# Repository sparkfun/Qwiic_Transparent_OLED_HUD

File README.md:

SparkFun Qwiic Transparent OLED HUD
========================================

[*SparkFun Qwiic Transparent OLED HUD Hookup Guide (LCD-15079)*](https://www.sparkfun.com/products/14691)

Qwiic Breakout for the WiseChip US-0011GMIAG01 OLED HUD. Clear screens are no longer a thing of the Sci-Fi world! The Qwiic Transparent OLED HUD is SparkFun's answer to all of your futuristic transparent HUD needs. Designed for use in vehicle heads-up displays, this OLED panel is brilliant in the dark but easily visible in daylight. The display is "area colored" meaning that while no one segment can change colors, there are different colored segments on the display.

Repository Contents
-------------------

* **/Hardware** - Eagle design files (.brd, .sch)
* **/Production** - Production panel files (.brd)

Documentation
--------------
* **[Library](https://github.com/sparkfun/SparkFun_WiseChip_HUD_Library)** - Arduino library
* **[Hookup Guide](https://learn.sparkfun.com/tutorials/qwiic-transparent-oled-hud-hookup-guide)** - Basic hookup guide

Product Versions
----------------

* **[LCD-15079](https://www.sparkfun.com/products/15079)** - SparkFun Red Version
* **[SPX-14691](https://www.sparkfun.com/products/14691)** - SparkX Version

License Information
-------------------

This product is _**open source**_! 

Please review the LICENSE.md file for license information. 

If you have any questions or concerns on licensing, please contact techsupport@sparkfun.com.

Distributed as-is; no warranty is given.

- Your friends at SparkFun.

_<COLLABORATION CREDIT>_

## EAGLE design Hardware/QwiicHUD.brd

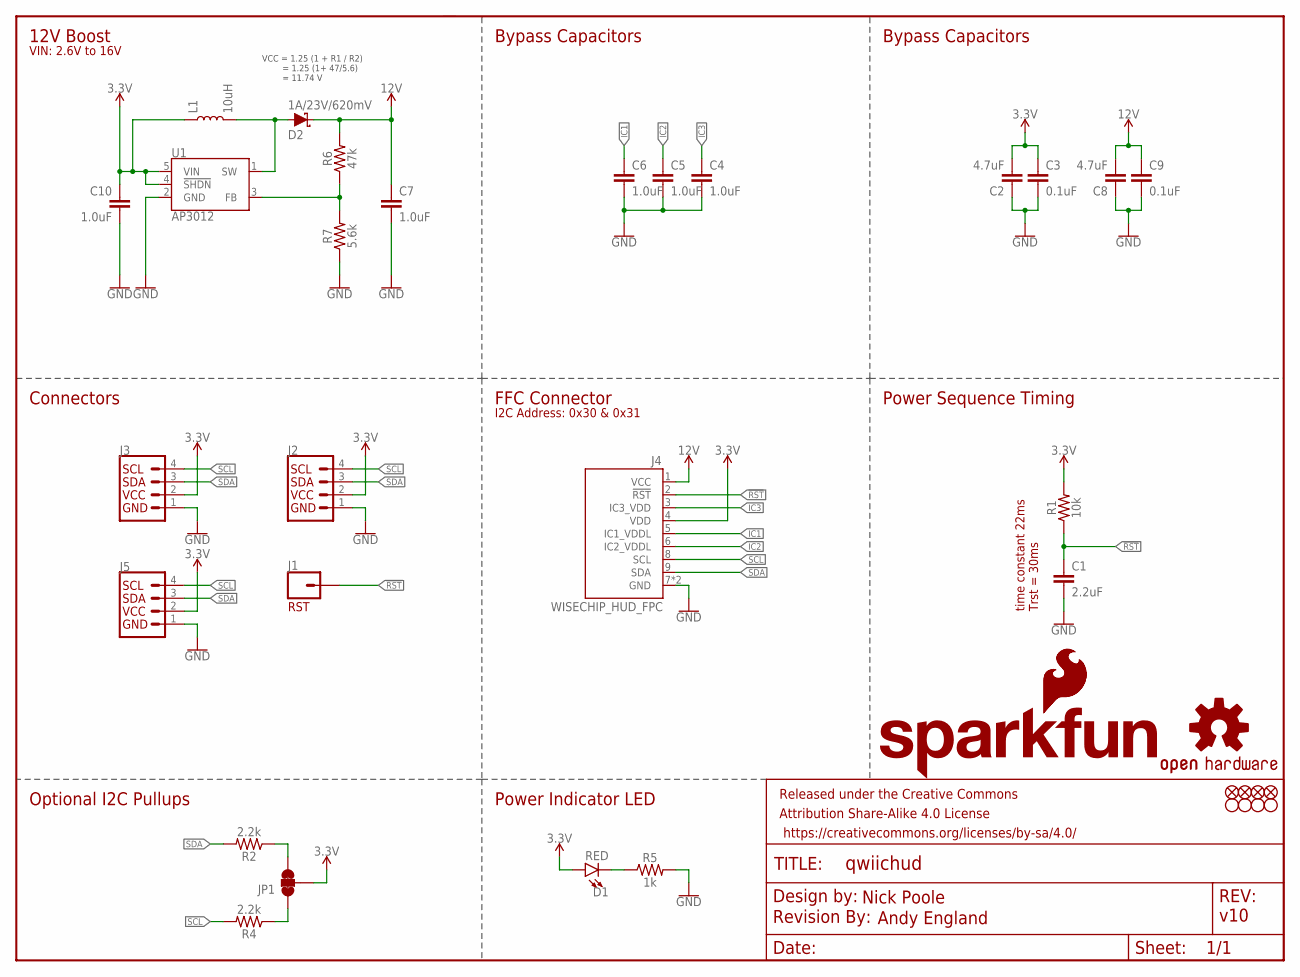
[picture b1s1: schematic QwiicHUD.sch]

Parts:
C1: 2.2uF; 0603
C2, C8: 4.7uF; 0603
C3, C9: 0.1uF; 0603
C4, C5, C6, C10: 1.0uF; 0603
C7: 1.0uF; 0805
D1: RED; LED-0603
D2: 1A/23V/620mV; SOD-323
FD1, FD2, FD3, FD4: FIDUCIALUFIDUCIAL; FIDUCIAL-MICRO
FRAME1: FRAME-LETTER; CREATIVE_COMMONS
H1, H2, H3, H4: STAND-OFF
J1: CONN_01PTH_NO_SILK_YES_STOP; 1X01_NO_SILK
J2: I2C_STANDARD_NO_SILK; 1X04_NO_SILK
J3, J5: QWIIC_CONNECTORJS-1MM; 1X04_1MM_RA
J4: WISECHIP_HUD_FPC; SERIES6288
JP1: JUMPER-SMT_3_2-NC_TRACE_SILK; SMT-JUMPER_3_2-NC_TRACE_SILK
L1: 10uH; INDUCTOR_4.7UH
LOGO1: OSHW-LOGOS; OSHW-LOGO-S
LOGO2: SFE_LOGO_NAME_FLAME.1_INCH; SFE_LOGO_NAME_FLAME_.1
LOGO3: SFE_LOGO_FLAME.1_INCH; SFE_LOGO_FLAME_.1
LOGO4: REVISION
R1: 10k; 0603
R2, R4: 2.2k; 0603
R5: 1k; 0603
R6: 47k; 0603
R7: 5.6k; 0603
U1: AP3012; SOT23-5

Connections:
3.3V: C2.2, C3.1, C10.1, D1.A, J2.2 (VCC), J3.2, J4.4 (VDD), J5.2, JP1.2, L1.P$1 (1), R1.2, U1.4 (!SHDN!), U1.5 (VIN)
12V: C7.1, C8.2, C9.1, D2.C, J4.1 (VCC), R6.2
!RST: C1.1, J1.1, J4.2 (!RST), R1.1
GND: C1.2, C2.1, C3.2, C4.2, C5.2, C6.2, C7.2, C8.1, C9.2, C10.2, J2.1 (GND), J3.1, J4.7 (GND), J4.10 (GND), J5.1, R5.2, R7.1, U1.2 (GND)
IC1: C6.1, J4.5 (IC1_VDDL)
IC2: C5.1, J4.6 (IC2_VDDL)
IC3: C4.1, J4.3 (IC3_VDD)
unnamed: JP1.3, R2.1
unnamed: JP1.1, R4.1
unnamed: D1.C, R5.1
unnamed: D2.A, L1.P$2 (2), U1.1 (SW)
unnamed: R6.1, R7.2, U1.3 (FB)
SCL: J2.4 (SCL), J3.4, J4.8 (SCL), J5.4, R4.2
SDA: J2.3 (SDA), J3.3, J4.9 (SDA), J5.3, R2.2

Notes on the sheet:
time constant 22ms Trst = 30ms
FFC Connector
Connectors
Power Sequence Timing
Optional I2C Pullups
RST
Power Indicator LED
VCC = 1.25 (1 + R1 / R2) = 1.25 (1+ 47/5.6) = 11.74 V
12V Boost
Nick Poole
Andy England
v10
VIN: 2.6V to 16V
I2C Address: 0x30 & 0x31
Bypass Capacitors

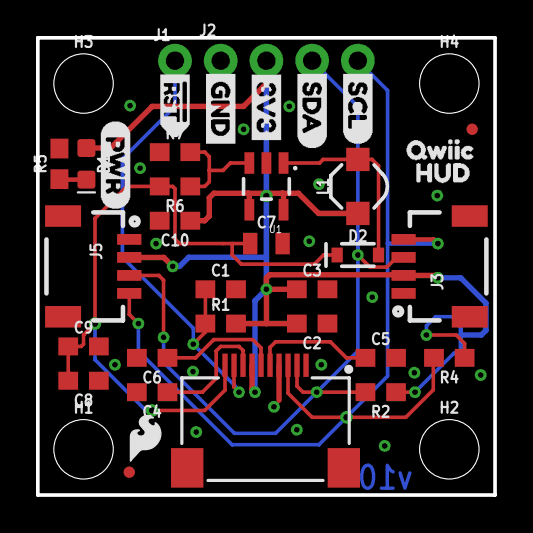
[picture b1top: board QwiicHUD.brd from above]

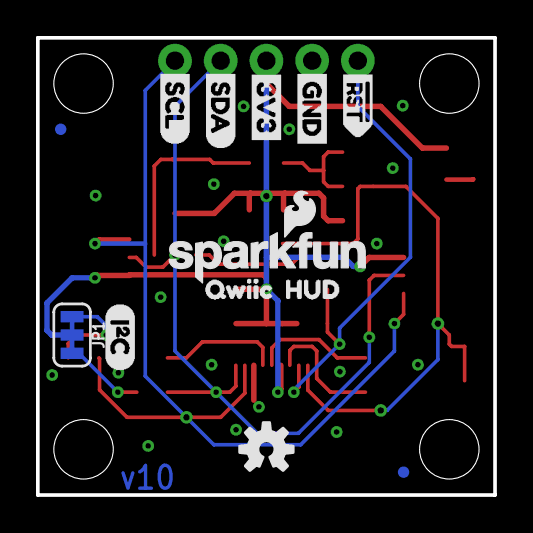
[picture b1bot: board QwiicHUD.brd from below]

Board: 2 copper layers, 25.4 x 25.4 mm, 55 parts (13 on the bottom side), 14 nets.

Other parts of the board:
U$1, U$14: #RST>
U$2, U$18: QWIIC0
U$3, U$19: HUD1
U$5, U$13: GND
U$6, U$12: 3V3
U$7, U$10: SDA
U$8, U$11: SCL
U$9: (PWR)
U$20: (I_SUPER2_C)

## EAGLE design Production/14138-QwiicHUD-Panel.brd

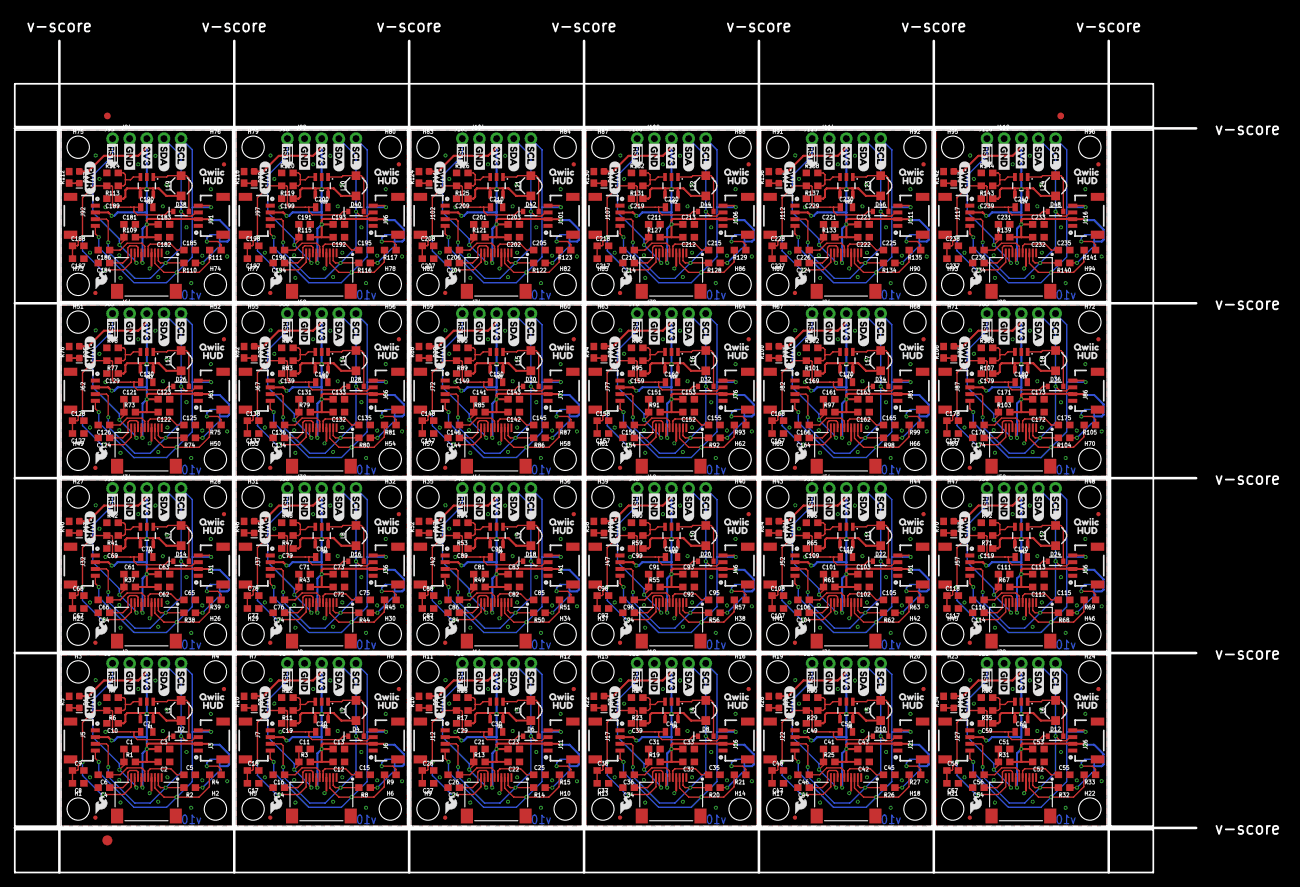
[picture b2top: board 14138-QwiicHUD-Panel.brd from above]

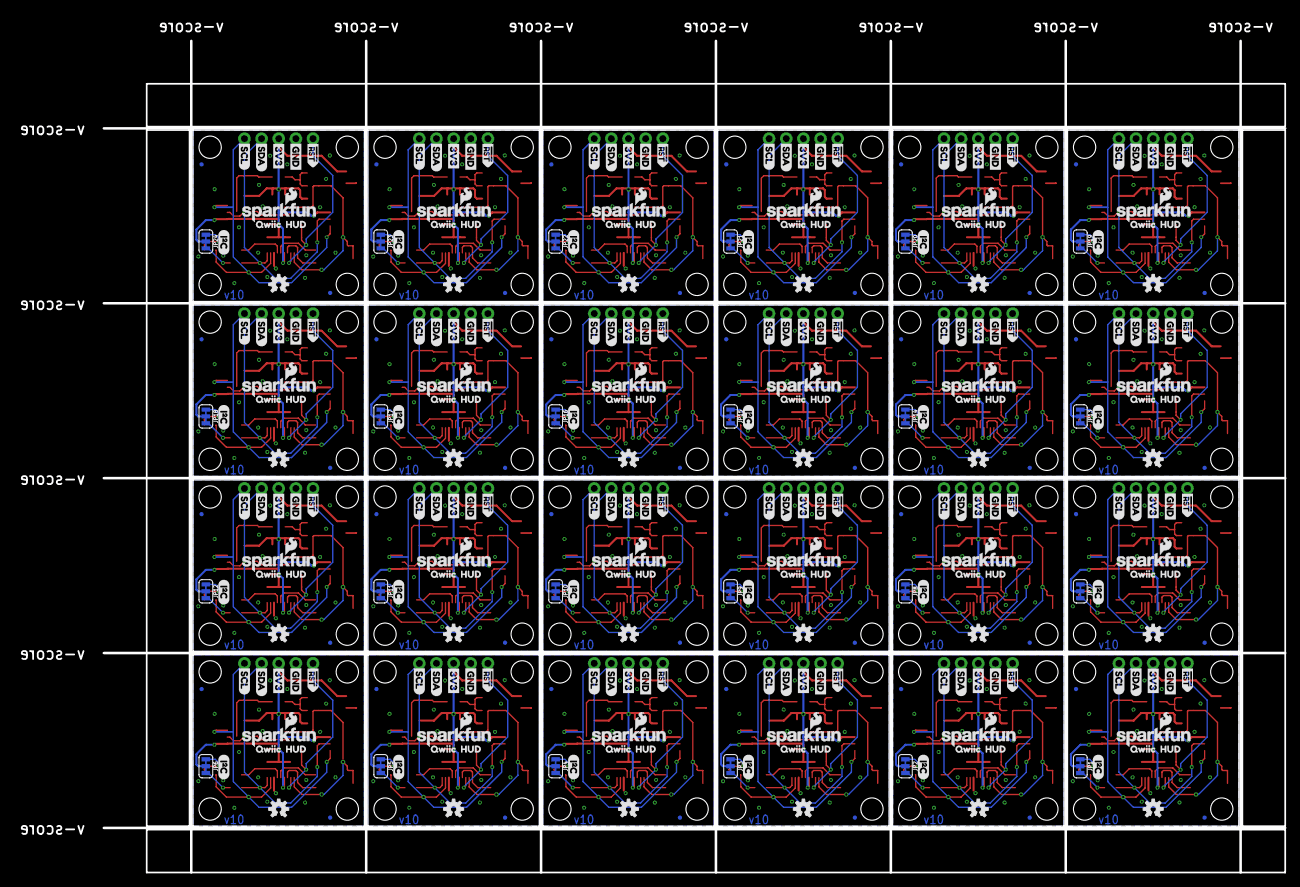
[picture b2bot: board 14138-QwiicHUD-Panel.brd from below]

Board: 2 copper layers, 188.2 x 127.1 mm, 1275 parts (312 on the bottom side), 336 nets.

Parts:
C1, C11, C21, C31, C41, C51, C61, C71, C81, C91, C101, C111, C121, C131, C141, C151, C161, C171, C181, C191, C201, C211, C221, C231: 2.2uF; 0603
C2, C8, C12, C17, C22, C27, C32, C37, C42, C47, C52, C57, C62, C67, C72, C77, C82, C87, C92, C97, C102, C107, C112, C117, C122, C127, C132, C137, C142, C147, C152, C157, C162, C167, C172, C177, C182, C187, C192, C197, C202, C207, C212, C217, C222, C227, C232, C237: 4.7uF; 0603
C3, C9, C13, C18, C23, C28, C33, C38, C43, C48, C53, C58, C63, C68, C73, C78, C83, C88, C93, C98, C103, C108, C113, C118, C123, C128, C133, C138, C143, C148, C153, C158, C163, C168, C173, C178, C183, C188, C193, C198, C203, C208, C213, C218, C223, C228, C233, C238: 0.1uF; 0603
C4, C5, C6, C10, C14, C15, C16, C19, C24, C25, C26, C29, C34, C35, C36, C39, C44, C45, C46, C49, C54, C55, C56, C59, C64, C65, C66, C69, C74, C75, C76, C79, C84, C85, C86, C89, C94, C95, C96, C99, C104, C105, C106, C109, C114, C115, C116, C119, C124, C125, C126, C129, C134, C135, C136, C139, C144, C145, C146, C149, C154, C155, C156, C159, C164, C165, C166, C169, C174, C175, C176, C179, C184, C185, C186, C189, C194, C195, C196, C199, C204, C205, C206, C209, C214, C215, C216, C219, C224, C225, C226, C229, C234, C235, C236, C239: 1.0uF; 0603
C7, C20, C30, C40, C50, C60, C70, C80, C90, C100, C110, C120, C130, C140, C150, C160, C170, C180, C190, C200, C210, C220, C230, C240: 1.0uF; 0805
D1, D3, D5, D7, D9, D11, D13, D15, D17, D19, D21, D23, D25, D27, D29, D31, D33, D35, D37, D39, D41, D43, D45, D47: RED; LED-0603
D2, D4, D6, D8, D10, D12, D14, D16, D18, D20, D22, D24, D26, D28, D30, D32, D34, D36, D38, D40, D42, D44, D46, D48: 1A/23V/620mV; SOD-323
E$1, E$2: FIDUCIAL-1X2
E$3: FIDUCIAL-1.5X3
FD1, FD2, FD3, FD4, FD5, FD6, FD7, FD8, FD9, FD10, FD11, FD12, FD13, FD14, FD15, FD16, FD17, FD18, FD19, FD20, FD21, FD22, FD23, FD24, FD25, FD26, FD27, FD28, FD29, FD30, FD31, FD32, FD33, FD34, FD35, FD36, FD37, FD38, FD39, FD40, FD41, FD42, FD43, FD44, FD45, FD46, FD47, FD48, FD49, FD50, FD51, FD52, FD53, FD54, FD55, FD56, FD57, FD58, FD59, FD60, FD61, FD62, FD63, FD64, FD65, FD66, FD67, FD68, FD69, FD70, FD71, FD72, FD73, FD74, FD75, FD76, FD77, FD78, FD79, FD80, FD81, FD82, FD83, FD84, FD85, FD86, FD87, FD88, FD89, FD90, FD91, FD92, FD93, FD94, FD95, FD96: FIDUCIALUFIDUCIAL; FIDUCIAL-MICRO
H1, H2, H3, H4, H5, H6, H7, H8, H9, H10, H11, H12, H13, H14, H15, H16, H17, H18, H19, H20, H21, H22, H23, H24, H25, H26, H27, H28, H29, H30, H31, H32, H33, H34, H35, H36, H37, H38, H39, H40, H41, H42, H43, H44, H45, H46, H47, H48, H49, H50, H51, H52, H53, H54, H55, H56, H57, H58, H59, H60, H61, H62, H63, H64, H65, H66, H67, H68, H69, H70, H71, H72, H73, H74, H75, H76, H77, H78, H79, H80, H81, H82, H83, H84, H85, H86, H87, H88, H89, H90, H91, H92, H93, H94, H95, H96: STAND-OFF
J1, J8, J13, J18, J23, J28, J33, J38, J43, J48, J53, J58, J63, J68, J73, J78, J83, J88, J93, J98, J103, J108, J113, J118: 1X01_NO_SILK
J2, J9, J14, J19, J24, J29, J34, J39, J44, J49, J54, J59, J64, J69, J74, J79, J84, J89, J94, J99, J104, J109, J114, J119: 1X04_NO_SILK
J3, J5, J6, J7, J11, J12, J16, J17, J21, J22, J26, J27, J31, J32, J36, J37, J41, J42, J46, J47, J51, J52, J56, J57, J61, J62, J66, J67, J71, J72, J76, J77, J81, J82, J86, J87, J91, J92, J96, J97, J101, J102, J106, J107, J111, J112, J116, J117: 1X04_1MM_RA
J4, J10, J15, J20, J25, J30, J35, J40, J45, J50, J55, J60, J65, J70, J75, J80, J85, J90, J95, J100, J105, J110, J115, J120: WISECHIP_HUD_FPC; SERIES6288
JP1, JP2, JP3, JP4, JP5, JP6, JP7, JP8, JP9, JP10, JP11, JP12, JP13, JP14, JP15, JP16, JP17, JP18, JP19, JP20, JP21, JP22, JP23, JP24: SMT-JUMPER_3_2-NC_TRACE_SILK
L1, L2, L3, L4, L5, L6, L7, L8, L9, L10, L11, L12, L13, L14, L15, L16, L17, L18, L19, L20, L21, L22, L23, L24: 10uH; INDUCTOR_4.7UH
LOGO1, LOGO6, LOGO9, LOGO12, LOGO15, LOGO18, LOGO21, LOGO24, LOGO27, LOGO30, LOGO33, LOGO36, LOGO39, LOGO42, LOGO45, LOGO48, LOGO51, LOGO54, LOGO57, LOGO60, LOGO63, LOGO66, LOGO69, LOGO72: OSHW-LOGOS; OSHW-LOGO-S
LOGO2, LOGO4, LOGO7, LOGO10, LOGO13, LOGO16, LOGO19, LOGO22, LOGO25, LOGO28, LOGO31, LOGO34, LOGO37, LOGO40, LOGO43, LOGO46, LOGO49, LOGO52, LOGO55, LOGO58, LOGO61, LOGO64, LOGO67, LOGO70: SFE_LOGO_NAME_FLAME.1_INCH; SFE_LOGO_NAME_FLAME_.1
LOGO3, LOGO5, LOGO8, LOGO11, LOGO14, LOGO17, LOGO20, LOGO23, LOGO26, LOGO29, LOGO32, LOGO35, LOGO38, LOGO41, LOGO44, LOGO47, LOGO50, LOGO53, LOGO56, LOGO59, LOGO62, LOGO65, LOGO68, LOGO71: SFE_LOGO_FLAME.1_INCH; SFE_LOGO_FLAME_.1
R1, R3, R13, R19, R25, R31, R37, R43, R49, R55, R61, R67, R73, R79, R85, R91, R97, R103, R109, R115, R121, R127, R133, R139: 10k; 0603
R2, R4, R8, R9, R14, R15, R20, R21, R26, R27, R32, R33, R38, R39, R44, R45, R50, R51, R56, R57, R62, R63, R68, R69, R74, R75, R80, R81, R86, R87, R92, R93, R98, R99, R104, R105, R110, R111, R116, R117, R122, R123, R128, R129, R134, R135, R140, R141: 2.2k; 0603
R5, R10, R16, R22, R28, R34, R40, R46, R52, R58, R64, R70, R76, R82, R88, R94, R100, R106, R112, R118, R124, R130, R136, R142: 1k; 0603
R6, R11, R17, R23, R29, R35, R41, R47, R53, R59, R65, R71, R77, R83, R89, R95, R101, R107, R113, R119, R125, R131, R137, R143: 47k; 0603
R7, R12, R18, R24, R30, R36, R42, R48, R54, R60, R66, R72, R78, R84, R90, R96, R102, R108, R114, R120, R126, R132, R138, R144: 5.6k; 0603
U1, U2, U3, U4, U5, U6, U7, U8, U9, U10, U11, U12, U13, U14, U15, U16, U17, U18, U19, U20, U21, U22, U23, U24: AP3012; SOT23-5
U$1, U$4, U$14, U$27, U$33, U$43, U$49, U$59, U$65, U$75, U$81, U$91, U$97, U$107, U$113, U$123, U$129, U$139, U$145, U$155, U$161, U$171, U$177, U$187, U$193, U$203, U$209, U$219, U$225, U$235, U$241, U$251, U$257, U$267, U$273, U$283, U$289, U$299, U$305, U$315, U$321, U$331, U$337, U$347, U$353, U$363, U$369, U$379: #RST>
U$2, U$18, U$28, U$31, U$44, U$47, U$60, U$63, U$76, U$79, U$92, U$95, U$108, U$111, U$124, U$127, U$140, U$143, U$156, U$159, U$172, U$175, U$188, U$191, U$204, U$207, U$220, U$223, U$236, U$239, U$252, U$255, U$268, U$271, U$284, U$287, U$300, U$303, U$316, U$319, U$332, U$335, U$348, U$351, U$364, U$367, U$380, U$383: QWIIC0
U$3, U$19, U$29, U$32, U$45, U$48, U$61, U$64, U$77, U$80, U$93, U$96, U$109, U$112, U$125, U$128, U$141, U$144, U$157, U$160, U$173, U$176, U$189, U$192, U$205, U$208, U$221, U$224, U$237, U$240, U$253, U$256, U$269, U$272, U$285, U$288, U$301, U$304, U$317, U$320, U$333, U$336, U$349, U$352, U$365, U$368, U$381, U$384: HUD1
U$5, U$13, U$15, U$26, U$34, U$42, U$50, U$58, U$66, U$74, U$82, U$90, U$98, U$106, U$114, U$122, U$130, U$138, U$146, U$154, U$162, U$170, U$178, U$186, U$194, U$202, U$210, U$218, U$226, U$234, U$242, U$250, U$258, U$266, U$274, U$282, U$290, U$298, U$306, U$314, U$322, U$330, U$338, U$346, U$354, U$362, U$370, U$378: GND
U$6, U$12, U$16, U$25, U$35, U$41, U$51, U$57, U$67, U$73, U$83, U$89, U$99, U$105, U$115, U$121, U$131, U$137, U$147, U$153, U$163, U$169, U$179, U$185, U$195, U$201, U$211, U$217, U$227, U$233, U$243, U$249, U$259, U$265, U$275, U$281, U$291, U$297, U$307, U$313, U$323, U$329, U$339, U$345, U$355, U$361, U$371, U$377: 3V3
U$7, U$10, U$17, U$23, U$36, U$39, U$52, U$55, U$68, U$71, U$84, U$87, U$100, U$103, U$116, U$119, U$132, U$135, U$148, U$151, U$164, U$167, U$180, U$183, U$196, U$199, U$212, U$215, U$228, U$231, U$244, U$247, U$260, U$263, U$276, U$279, U$292, U$295, U$308, U$311, U$324, U$327, U$340, U$343, U$356, U$359, U$372, U$375: SDA
U$8, U$11, U$21, U$24, U$37, U$40, U$53, U$56, U$69, U$72, U$85, U$88, U$101, U$104, U$117, U$120, U$133, U$136, U$149, U$152, U$165, U$168, U$181, U$184, U$197, U$200, U$213, U$216, U$229, U$232, U$245, U$248, U$261, U$264, U$277, U$280, U$293, U$296, U$309, U$312, U$325, U$328, U$341, U$344, U$357, U$360, U$373, U$376: SCL
U$9, U$22, U$38, U$54, U$70, U$86, U$102, U$118, U$134, U$150, U$166, U$182, U$198, U$214, U$230, U$246, U$262, U$278, U$294, U$310, U$326, U$342, U$358, U$374: (PWR)
U$20, U$30, U$46, U$62, U$78, U$94, U$110, U$126, U$142, U$158, U$174, U$190, U$206, U$222, U$238, U$254, U$270, U$286, U$302, U$318, U$334, U$350, U$366, U$382: (I_SUPER2_C)

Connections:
3.3V: C2.2, C3.1, C10.1, D1.A, J2.2, J3.2, J4.4, J5.2, JP1.2, L1.P$1, R1.2, U1.4, U1.5
3.3V1: C12.2, C13.1, C19.1, D3.A, J6.2, J7.2, J9.2, J10.4, JP2.2, L2.P$1, R3.2, U2.4, U2.5
3.3V2: C22.2, C23.1, C29.1, D5.A, J11.2, J12.2, J14.2, J15.4, JP3.2, L3.P$1, R13.2, U3.4, U3.5
3.3V3: C32.2, C33.1, C39.1, D7.A, J16.2, J17.2, J19.2, J20.4, JP4.2, L4.P$1, R19.2, U4.4, U4.5
3.3V4: C42.2, C43.1, C49.1, D9.A, J21.2, J22.2, J24.2, J25.4, JP5.2, L5.P$1, R25.2, U5.4, U5.5
3.3V5: C52.2, C53.1, C59.1, D11.A, J26.2, J27.2, J29.2, J30.4, JP6.2, L6.P$1, R31.2, U6.4, U6.5
3.3V6: C62.2, C63.1, C69.1, D13.A, J31.2, J32.2, J34.2, J35.4, JP7.2, L7.P$1, R37.2, U7.4, U7.5
3.3V7: C72.2, C73.1, C79.1, D15.A, J36.2, J37.2, J39.2, J40.4, JP8.2, L8.P$1, R43.2, U8.4, U8.5
3.3V8: C82.2, C83.1, C89.1, D17.A, J41.2, J42.2, J44.2, J45.4, JP9.2, L9.P$1, R49.2, U9.4, U9.5
3.3V9: C92.2, C93.1, C99.1, D19.A, J46.2, J47.2, J49.2, J50.4, JP10.2, L10.P$1, R55.2, U10.4, U10.5
3.3V10: C102.2, C103.1, C109.1, D21.A, J51.2, J52.2, J54.2, J55.4, JP11.2, L11.P$1, R61.2, U11.4, U11.5
3.3V11: C112.2, C113.1, C119.1, D23.A, J56.2, J57.2, J59.2, J60.4, JP12.2, L12.P$1, R67.2, U12.4, U12.5
3.3V12: C122.2, C123.1, C129.1, D25.A, J61.2, J62.2, J64.2, J65.4, JP13.2, L13.P$1, R73.2, U13.4, U13.5
3.3V13: C132.2, C133.1, C139.1, D27.A, J66.2, J67.2, J69.2, J70.4, JP14.2, L14.P$1, R79.2, U14.4, U14.5
3.3V14: C142.2, C143.1, C149.1, D29.A, J71.2, J72.2, J74.2, J75.4, JP15.2, L15.P$1, R85.2, U15.4, U15.5
3.3V15: C152.2, C153.1, C159.1, D31.A, J76.2, J77.2, J79.2, J80.4, JP16.2, L16.P$1, R91.2, U16.4, U16.5
3.3V16: C162.2, C163.1, C169.1, D33.A, J81.2, J82.2, J84.2, J85.4, JP17.2, L17.P$1, R97.2, U17.4, U17.5
3.3V17: C172.2, C173.1, C179.1, D35.A, J86.2, J87.2, J89.2, J90.4, JP18.2, L18.P$1, R103.2, U18.4, U18.5
3.3V18: C182.2, C183.1, C189.1, D37.A, J91.2, J92.2, J94.2, J95.4, JP19.2, L19.P$1, R109.2, U19.4, U19.5
3.3V19: C192.2, C193.1, C199.1, D39.A, J96.2, J97.2, J99.2, J100.4, JP20.2, L20.P$1, R115.2, U20.4, U20.5
3.3V20: C202.2, C203.1, C209.1, D41.A, J101.2, J102.2, J104.2, J105.4, JP21.2, L21.P$1, R121.2, U21.4, U21.5
3.3V21: C212.2, C213.1, C219.1, D43.A, J106.2, J107.2, J109.2, J110.4, JP22.2, L22.P$1, R127.2, U22.4, U22.5
3.3V22: C222.2, C223.1, C229.1, D45.A, J111.2, J112.2, J114.2, J115.4, JP23.2, L23.P$1, R133.2, U23.4, U23.5
3.3V23: C232.2, C233.1, C239.1, D47.A, J116.2, J117.2, J119.2, J120.4, JP24.2, L24.P$1, R139.2, U24.4, U24.5
12V: C7.1, C8.2, C9.1, D2.C, J4.1, R6.2
12V1: C17.2, C18.1, C20.1, D4.C, J10.1, R11.2
12V2: C27.2, C28.1, C30.1, D6.C, J15.1, R17.2
12V3: C37.2, C38.1, C40.1, D8.C, J20.1, R23.2
12V4: C47.2, C48.1, C50.1, D10.C, J25.1, R29.2
12V5: C57.2, C58.1, C60.1, D12.C, J30.1, R35.2
12V6: C67.2, C68.1, C70.1, D14.C, J35.1, R41.2
12V7: C77.2, C78.1, C80.1, D16.C, J40.1, R47.2
12V8: C87.2, C88.1, C90.1, D18.C, J45.1, R53.2
12V9: C97.2, C98.1, C100.1, D20.C, J50.1, R59.2
12V10: C107.2, C108.1, C110.1, D22.C, J55.1, R65.2
12V11: C117.2, C118.1, C120.1, D24.C, J60.1, R71.2
12V12: C127.2, C128.1, C130.1, D26.C, J65.1, R77.2
12V13: C137.2, C138.1, C140.1, D28.C, J70.1, R83.2
12V14: C147.2, C148.1, C150.1, D30.C, J75.1, R89.2
12V15: C157.2, C158.1, C160.1, D32.C, J80.1, R95.2
12V16: C167.2, C168.1, C170.1, D34.C, J85.1, R101.2
12V17: C177.2, C178.1, C180.1, D36.C, J90.1, R107.2
12V18: C187.2, C188.1, C190.1, D38.C, J95.1, R113.2
12V19: C197.2, C198.1, C200.1, D40.C, J100.1, R119.2
12V20: C207.2, C208.1, C210.1, D42.C, J105.1, R125.2
12V21: C217.2, C218.1, C220.1, D44.C, J110.1, R131.2
12V22: C227.2, C228.1, C230.1, D46.C, J115.1, R137.2
12V23: C237.2, C238.1, C240.1, D48.C, J120.1, R143.2
!RST: C1.1, J1.1, J4.2, R1.1
!RST1: C11.1, J8.1, J10.2, R3.1
!RST2: C21.1, J13.1, J15.2, R13.1
!RST3: C31.1, J18.1, J20.2, R19.1
!RST4: C41.1, J23.1, J25.2, R25.1
!RST5: C51.1, J28.1, J30.2, R31.1
!RST6: C61.1, J33.1, J35.2, R37.1
!RST7: C71.1, J38.1, J40.2, R43.1
!RST8: C81.1, J43.1, J45.2, R49.1
!RST9: C91.1, J48.1, J50.2, R55.1
!RST10: C101.1, J53.1, J55.2, R61.1
!RST11: C111.1, J58.1, J60.2, R67.1
!RST12: C121.1, J63.1, J65.2, R73.1
!RST13: C131.1, J68.1, J70.2, R79.1
!RST14: C141.1, J73.1, J75.2, R85.1
!RST15: C151.1, J78.1, J80.2, R91.1
!RST16: C161.1, J83.1, J85.2, R97.1
!RST17: C171.1, J88.1, J90.2, R103.1
!RST18: C181.1, J93.1, J95.2, R109.1
!RST19: C191.1, J98.1, J100.2, R115.1
!RST20: C201.1, J103.1, J105.2, R121.1
!RST21: C211.1, J108.1, J110.2, R127.1
!RST22: C221.1, J113.1, J115.2, R133.1
!RST23: C231.1, J118.1, J120.2, R139.1
GND: C1.2, C2.1, C3.2, C4.2, C5.2, C6.2, C7.2, C8.1, C9.2, C10.2, J2.1, J3.1, J4.7, J4.10, J5.1, R5.2, R7.1, U1.2
GND1: C11.2, C12.1, C13.2, C14.2, C15.2, C16.2, C17.1, C18.2, C19.2, C20.2, J6.1, J7.1, J9.1, J10.7, J10.10, R10.2, R12.1, U2.2
GND2: C21.2, C22.1, C23.2, C24.2, C25.2, C26.2, C27.1, C28.2, C29.2, C30.2, J11.1, J12.1, J14.1, J15.7, J15.10, R16.2, R18.1, U3.2
GND3: C31.2, C32.1, C33.2, C34.2, C35.2, C36.2, C37.1, C38.2, C39.2, C40.2, J16.1, J17.1, J19.1, J20.7, J20.10, R22.2, R24.1, U4.2
GND4: C41.2, C42.1, C43.2, C44.2, C45.2, C46.2, C47.1, C48.2, C49.2, C50.2, J21.1, J22.1, J24.1, J25.7, J25.10, R28.2, R30.1, U5.2
GND5: C51.2, C52.1, C53.2, C54.2, C55.2, C56.2, C57.1, C58.2, C59.2, C60.2, J26.1, J27.1, J29.1, J30.7, J30.10, R34.2, R36.1, U6.2
GND6: C61.2, C62.1, C63.2, C64.2, C65.2, C66.2, C67.1, C68.2, C69.2, C70.2, J31.1, J32.1, J34.1, J35.7, J35.10, R40.2, R42.1, U7.2
GND7: C71.2, C72.1, C73.2, C74.2, C75.2, C76.2, C77.1, C78.2, C79.2, C80.2, J36.1, J37.1, J39.1, J40.7, J40.10, R46.2, R48.1, U8.2
GND8: C81.2, C82.1, C83.2, C84.2, C85.2, C86.2, C87.1, C88.2, C89.2, C90.2, J41.1, J42.1, J44.1, J45.7, J45.10, R52.2, R54.1, U9.2
GND9: C91.2, C92.1, C93.2, C94.2, C95.2, C96.2, C97.1, C98.2, C99.2, C100.2, J46.1, J47.1, J49.1, J50.7, J50.10, R58.2, R60.1, U10.2
GND10: C101.2, C102.1, C103.2, C104.2, C105.2, C106.2, C107.1, C108.2, C109.2, C110.2, J51.1, J52.1, J54.1, J55.7, J55.10, R64.2, R66.1, U11.2
GND11: C111.2, C112.1, C113.2, C114.2, C115.2, C116.2, C117.1, C118.2, C119.2, C120.2, J56.1, J57.1, J59.1, J60.7, J60.10, R70.2, R72.1, U12.2
GND12: C121.2, C122.1, C123.2, C124.2, C125.2, C126.2, C127.1, C128.2, C129.2, C130.2, J61.1, J62.1, J64.1, J65.7, J65.10, R76.2, R78.1, U13.2
GND13: C131.2, C132.1, C133.2, C134.2, C135.2, C136.2, C137.1, C138.2, C139.2, C140.2, J66.1, J67.1, J69.1, J70.7, J70.10, R82.2, R84.1, U14.2
GND14: C141.2, C142.1, C143.2, C144.2, C145.2, C146.2, C147.1, C148.2, C149.2, C150.2, J71.1, J72.1, J74.1, J75.7, J75.10, R88.2, R90.1, U15.2
GND15: C151.2, C152.1, C153.2, C154.2, C155.2, C156.2, C157.1, C158.2, C159.2, C160.2, J76.1, J77.1, J79.1, J80.7, J80.10, R94.2, R96.1, U16.2
GND16: C161.2, C162.1, C163.2, C164.2, C165.2, C166.2, C167.1, C168.2, C169.2, C170.2, J81.1, J82.1, J84.1, J85.7, J85.10, R100.2, R102.1, U17.2
GND17: C171.2, C172.1, C173.2, C174.2, C175.2, C176.2, C177.1, C178.2, C179.2, C180.2, J86.1, J87.1, J89.1, J90.7, J90.10, R106.2, R108.1, U18.2
GND18: C181.2, C182.1, C183.2, C184.2, C185.2, C186.2, C187.1, C188.2, C189.2, C190.2, J91.1, J92.1, J94.1, J95.7, J95.10, R112.2, R114.1, U19.2
GND19: C191.2, C192.1, C193.2, C194.2, C195.2, C196.2, C197.1, C198.2, C199.2, C200.2, J96.1, J97.1, J99.1, J100.7, J100.10, R118.2, R120.1, U20.2
GND20: C201.2, C202.1, C203.2, C204.2, C205.2, C206.2, C207.1, C208.2, C209.2, C210.2, J101.1, J102.1, J104.1, J105.7, J105.10, R124.2, R126.1, U21.2
GND21: C211.2, C212.1, C213.2, C214.2, C215.2, C216.2, C217.1, C218.2, C219.2, C220.2, J106.1, J107.1, J109.1, J110.7, J110.10, R130.2, R132.1, U22.2
GND22: C221.2, C222.1, C223.2, C224.2, C225.2, C226.2, C227.1, C228.2, C229.2, C230.2, J111.1, J112.1, J114.1, J115.7, J115.10, R136.2, R138.1, U23.2
GND23: C231.2, C232.1, C233.2, C234.2, C235.2, C236.2, C237.1, C238.2, C239.2, C240.2, J116.1, J117.1, J119.1, J120.7, J120.10, R142.2, R144.1, U24.2
IC1: C6.1, J4.5
IC2: C5.1, J4.6
IC3: C4.1, J4.3
IC4: C14.1, J10.3
IC5: C16.1, J10.5
IC6: C15.1, J10.6
IC7: C24.1, J15.3
IC8: C26.1, J15.5
IC9: C25.1, J15.6
IC10: C34.1, J20.3
IC11: C36.1, J20.5
IC12: C35.1, J20.6
IC13: C44.1, J25.3
IC14: C46.1, J25.5
IC15: C45.1, J25.6
IC16: C54.1, J30.3
IC17: C56.1, J30.5
IC18: C55.1, J30.6
IC19: C64.1, J35.3
IC20: C66.1, J35.5
IC21: C65.1, J35.6
IC22: C74.1, J40.3
IC23: C76.1, J40.5
IC24: C75.1, J40.6
IC25: C84.1, J45.3
IC26: C86.1, J45.5
IC27: C85.1, J45.6
IC28: C94.1, J50.3
IC29: C96.1, J50.5
IC30: C95.1, J50.6
IC31: C104.1, J55.3
IC32: C106.1, J55.5
IC33: C105.1, J55.6
IC34: C114.1, J60.3
IC35: C116.1, J60.5
IC36: C115.1, J60.6
IC37: C124.1, J65.3
IC38: C126.1, J65.5
IC39: C125.1, J65.6
IC40: C134.1, J70.3
IC41: C136.1, J70.5
IC42: C135.1, J70.6
IC43: C144.1, J75.3
IC44: C146.1, J75.5
IC45: C145.1, J75.6
IC46: C154.1, J80.3
IC47: C156.1, J80.5
IC48: C155.1, J80.6
IC49: C164.1, J85.3
IC50: C166.1, J85.5
IC51: C165.1, J85.6
IC52: C174.1, J90.3
IC53: C176.1, J90.5
IC54: C175.1, J90.6
IC55: C184.1, J95.3
IC56: C186.1, J95.5
IC57: C185.1, J95.6
IC58: C194.1, J100.3
IC59: C196.1, J100.5
IC60: C195.1, J100.6
IC61: C204.1, J105.3
IC62: C206.1, J105.5
IC63: C205.1, J105.6
IC64: C214.1, J110.3
IC65: C216.1, J110.5
IC66: C215.1, J110.6
IC67: C224.1, J115.3
IC68: C226.1, J115.5
IC69: C225.1, J115.6
IC70: C234.1, J120.3
IC71: C236.1, J120.5
IC72: C235.1, J120.6
unnamed: JP1.3, R2.1
unnamed: JP1.1, R4.1
unnamed: D1.C, R5.1
unnamed: D2.A, L1.P$2, U1.1
unnamed: R6.1, R7.2, U1.3
unnamed: JP2.3, R8.1
unnamed: JP2.1, R9.1
unnamed: D3.C, R10.1
unnamed: D4.A, L2.P$2, U2.1
unnamed: R11.1, R12.2, U2.3
unnamed: JP3.3, R14.1
unnamed: JP3.1, R15.1
unnamed: D5.C, R16.1
unnamed: D6.A, L3.P$2, U3.1
unnamed: R17.1, R18.2, U3.3
unnamed: JP4.3, R20.1
unnamed: JP4.1, R21.1
unnamed: D7.C, R22.1
unnamed: D8.A, L4.P$2, U4.1
unnamed: R23.1, R24.2, U4.3
unnamed: JP5.3, R26.1
unnamed: JP5.1, R27.1
unnamed: D9.C, R28.1
unnamed: D10.A, L5.P$2, U5.1
unnamed: R29.1, R30.2, U5.3
unnamed: JP6.3, R32.1
unnamed: JP6.1, R33.1
unnamed: D11.C, R34.1
unnamed: D12.A, L6.P$2, U6.1
unnamed: R35.1, R36.2, U6.3
unnamed: JP7.3, R38.1
unnamed: JP7.1, R39.1
unnamed: D13.C, R40.1
unnamed: D14.A, L7.P$2, U7.1
unnamed: R41.1, R42.2, U7.3
unnamed: JP8.3, R44.1
unnamed: JP8.1, R45.1
unnamed: D15.C, R46.1
unnamed: D16.A, L8.P$2, U8.1
unnamed: R47.1, R48.2, U8.3
unnamed: JP9.3, R50.1
unnamed: JP9.1, R51.1
unnamed: D17.C, R52.1
unnamed: D18.A, L9.P$2, U9.1
unnamed: R53.1, R54.2, U9.3
unnamed: JP10.3, R56.1
unnamed: JP10.1, R57.1
unnamed: D19.C, R58.1
unnamed: D20.A, L10.P$2, U10.1
unnamed: R59.1, R60.2, U10.3
unnamed: JP11.3, R62.1
unnamed: JP11.1, R63.1
unnamed: D21.C, R64.1
unnamed: D22.A, L11.P$2, U11.1
unnamed: R65.1, R66.2, U11.3
unnamed: JP12.3, R68.1
unnamed: JP12.1, R69.1
unnamed: D23.C, R70.1
unnamed: D24.A, L12.P$2, U12.1
unnamed: R71.1, R72.2, U12.3
unnamed: JP13.3, R74.1
unnamed: JP13.1, R75.1
unnamed: D25.C, R76.1
unnamed: D26.A, L13.P$2, U13.1
unnamed: R77.1, R78.2, U13.3
unnamed: JP14.3, R80.1
unnamed: JP14.1, R81.1
unnamed: D27.C, R82.1
unnamed: D28.A, L14.P$2, U14.1
unnamed: R83.1, R84.2, U14.3
unnamed: JP15.3, R86.1
unnamed: JP15.1, R87.1
unnamed: D29.C, R88.1
unnamed: D30.A, L15.P$2, U15.1
unnamed: R89.1, R90.2, U15.3
unnamed: JP16.3, R92.1
unnamed: JP16.1, R93.1
unnamed: D31.C, R94.1
unnamed: D32.A, L16.P$2, U16.1
unnamed: R95.1, R96.2, U16.3
unnamed: JP17.3, R98.1
unnamed: JP17.1, R99.1
unnamed: D33.C, R100.1
unnamed: D34.A, L17.P$2, U17.1
unnamed: R101.1, R102.2, U17.3
unnamed: JP18.3, R104.1
unnamed: JP18.1, R105.1
unnamed: D35.C, R106.1
unnamed: D36.A, L18.P$2, U18.1
unnamed: R107.1, R108.2, U18.3
unnamed: JP19.3, R110.1
unnamed: JP19.1, R111.1
unnamed: D37.C, R112.1
unnamed: D38.A, L19.P$2, U19.1
unnamed: R113.1, R114.2, U19.3
unnamed: JP20.3, R116.1
unnamed: JP20.1, R117.1
unnamed: D39.C, R118.1
unnamed: D40.A, L20.P$2, U20.1
unnamed: R119.1, R120.2, U20.3
unnamed: JP21.3, R122.1
unnamed: JP21.1, R123.1
unnamed: D41.C, R124.1
unnamed: D42.A, L21.P$2, U21.1
unnamed: R125.1, R126.2, U21.3
unnamed: JP22.3, R128.1
unnamed: JP22.1, R129.1
unnamed: D43.C, R130.1
unnamed: D44.A, L22.P$2, U22.1
unnamed: R131.1, R132.2, U22.3
unnamed: JP23.3, R134.1
unnamed: JP23.1, R135.1
unnamed: D45.C, R136.1
unnamed: D46.A, L23.P$2, U23.1
unnamed: R137.1, R138.2, U23.3
unnamed: JP24.3, R140.1
unnamed: JP24.1, R141.1
unnamed: D47.C, R142.1
unnamed: D48.A, L24.P$2, U24.1
unnamed: R143.1, R144.2, U24.3
SCL: J2.4, J3.4, J4.8, J5.4, R4.2
SCL1: J6.4, J7.4, J9.4, J10.8, R9.2
SCL2: J11.4, J12.4, J14.4, J15.8, R15.2
SCL3: J16.4, J17.4, J19.4, J20.8, R21.2
SCL4: J21.4, J22.4, J24.4, J25.8, R27.2
SCL5: J26.4, J27.4, J29.4, J30.8, R33.2
SCL6: J31.4, J32.4, J34.4, J35.8, R39.2
SCL7: J36.4, J37.4, J39.4, J40.8, R45.2
SCL8: J41.4, J42.4, J44.4, J45.8, R51.2
SCL9: J46.4, J47.4, J49.4, J50.8, R57.2
SCL10: J51.4, J52.4, J54.4, J55.8, R63.2
SCL11: J56.4, J57.4, J59.4, J60.8, R69.2
SCL12: J61.4, J62.4, J64.4, J65.8, R75.2
SCL13: J66.4, J67.4, J69.4, J70.8, R81.2
SCL14: J71.4, J72.4, J74.4, J75.8, R87.2
SCL15: J76.4, J77.4, J79.4, J80.8, R93.2
SCL16: J81.4, J82.4, J84.4, J85.8, R99.2
SCL17: J86.4, J87.4, J89.4, J90.8, R105.2
SCL18: J91.4, J92.4, J94.4, J95.8, R111.2
SCL19: J96.4, J97.4, J99.4, J100.8, R117.2
SCL20: J101.4, J102.4, J104.4, J105.8, R123.2
SCL21: J106.4, J107.4, J109.4, J110.8, R129.2
SCL22: J111.4, J112.4, J114.4, J115.8, R135.2
SCL23: J116.4, J117.4, J119.4, J120.8, R141.2
SDA: J2.3, J3.3, J4.9, J5.3, R2.2
SDA1: J6.3, J7.3, J9.3, J10.9, R8.2
SDA2: J11.3, J12.3, J14.3, J15.9, R14.2
SDA3: J16.3, J17.3, J19.3, J20.9, R20.2
SDA4: J21.3, J22.3, J24.3, J25.9, R26.2
SDA5: J26.3, J27.3, J29.3, J30.9, R32.2
SDA6: J31.3, J32.3, J34.3, J35.9, R38.2
SDA7: J36.3, J37.3, J39.3, J40.9, R44.2
SDA8: J41.3, J42.3, J44.3, J45.9, R50.2
SDA9: J46.3, J47.3, J49.3, J50.9, R56.2
SDA10: J51.3, J52.3, J54.3, J55.9, R62.2
SDA11: J56.3, J57.3, J59.3, J60.9, R68.2
SDA12: J61.3, J62.3, J64.3, J65.9, R74.2
SDA13: J66.3, J67.3, J69.3, J70.9, R80.2
SDA14: J71.3, J72.3, J74.3, J75.9, R86.2
SDA15: J76.3, J77.3, J79.3, J80.9, R92.2
SDA16: J81.3, J82.3, J84.3, J85.9, R98.2
SDA17: J86.3, J87.3, J89.3, J90.9, R104.2
SDA18: J91.3, J92.3, J94.3, J95.9, R110.2
SDA19: J96.3, J97.3, J99.3, J100.9, R116.2
SDA20: J101.3, J102.3, J104.3, J105.9, R122.2
SDA21: J106.3, J107.3, J109.3, J110.9, R128.2
SDA22: J111.3, J112.3, J114.3, J115.9, R134.2
SDA23: J116.3, J117.3, J119.3, J120.9, R140.2

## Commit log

2018-11-07 post design review
2018-11-09 post checklist changes
2018-11-13 updating bom
2018-11-15 Created panel v10

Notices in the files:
parts and their libraries:
SparkFun-Capacitors: Licensing: Creative Commons ShareAlike 4.0 International - https://creativecommons.org/licenses/by-sa/4.0
SparkFun-Aesthetics: Released under the Creative Commons Attribution Share-Alike 4.0 License
SparkFun-Aesthetics: https://creativecommons.org/licenses/by-sa/4.0
